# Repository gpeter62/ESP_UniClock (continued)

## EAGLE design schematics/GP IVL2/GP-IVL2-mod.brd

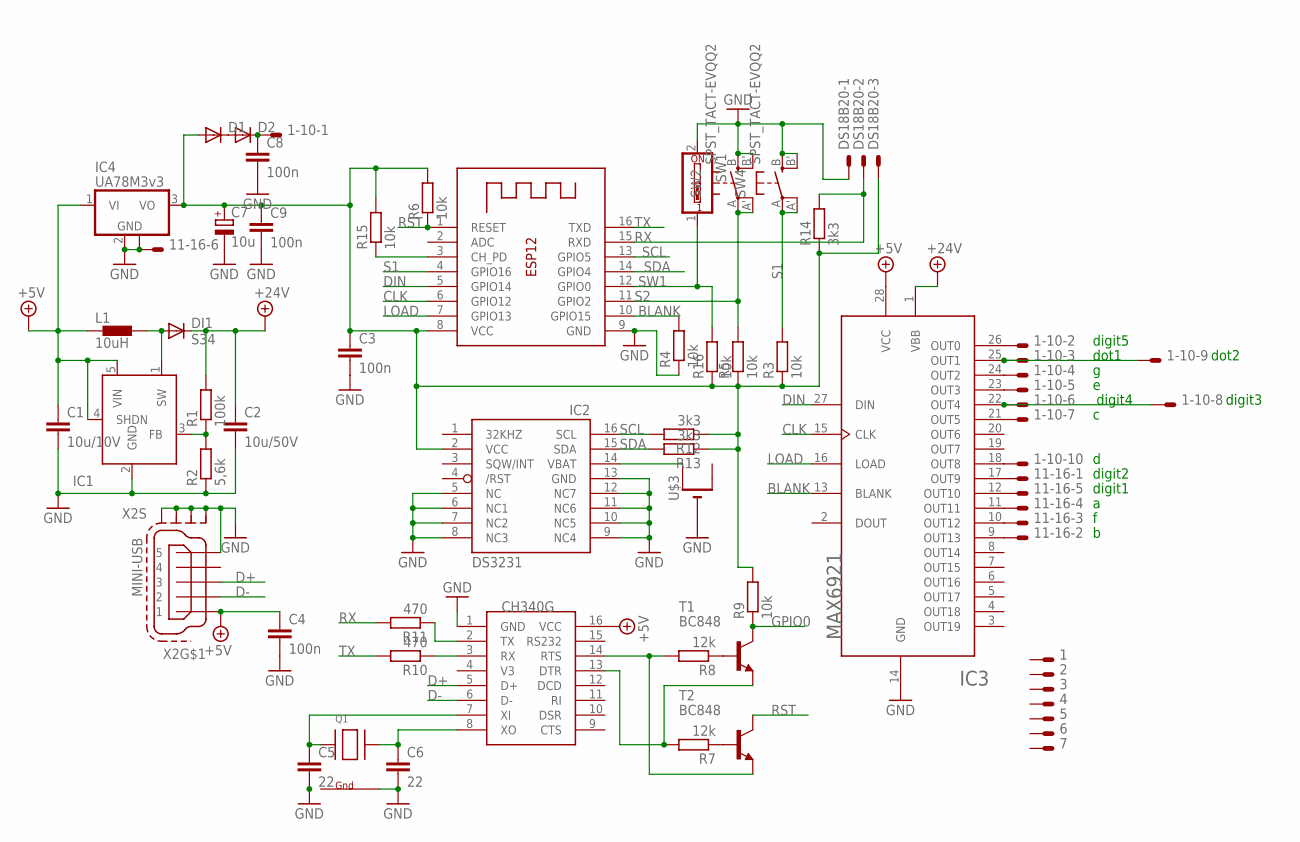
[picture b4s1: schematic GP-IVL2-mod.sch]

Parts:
1: 1; PAD1
1-10: 1-10; PAD10
2: 2; PAD1
3: 3; PAD1
4: 4; PAD1
5: 5; PAD1
6: 6; PAD1
7: 7; PAD1
11-16: 11-16; PAD6
C1: 10u/10V; 1206
C2: 10u/50V; 1206
C3, C4, C8, C9: 100n; C0603
C5, C6: 22; C0603
C7: 10u; E1,8-4
D1, D2: DIODE-D-7.5; D-7.5
DI1: S34; DI-214
DS18B20: PAD3
IC1: LT1930; SOT23-5
IC2: DS3231/SO; SO16W
IC3: MAX6921; SO-28W
IC4: UA78M3v3; SOT223
L1: 10uH; DR73A
Q1: XTAL-4-3225; NX3225
R1: 100k; 0603
R2: 5,6k; 0603
R3, R4, R5, R6, R9, R15, R16: 10k; R0603
R7, R8: 12k; R0603
R10, R11: 470; R0603
R12, R13: 3k3; R0603
R14: 3k3; MINI_MELF-0102W
SW1: SW_DIP-1; EDG-01
SW2, SW4: SPST_TACT-EVQQ2; EVQ-Q2
T1, T2: BC848; SOT23
U$1: CH340G; SOIC16
U$3: CR1220SMT; CR1220-SMD
X1: ESP-12
X2: MINI-USB; 32005-201

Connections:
+5V: C1.1, C4.1, IC1.4 (SHDN), IC1.5 (VIN), IC3.28 (VCC), IC4.1 (VI), L1.1, U$1.16 (VCC), X2.1
BLANK: IC3.13 (BLANK), R4.2, X1.10 (GPIO15)
CLK: IC3.15 (CLK), X1.6 (GPIO12)
D+: U$1.5 (D+), X2.3
D-: U$1.6 (D-), X2.2
DIN: IC3.27 (DIN), X1.5 (GPIO14)
G1: Q1.4 (G1)
GND: 11-16.P$6, C1.2, C2.2, C3.2, C4.2, C5.2, C6.2, C7.-, C8.2, C9.2, DS18B20.P$1, IC1.2 (GND), IC2.5 (NC), IC2.6 (NC1), IC2.7 (NC2), IC2.8 (NC3), IC2.9 (NC4), IC2.10 (NC5), IC2.11 (NC6), IC2.12 (NC7), IC2.13 (GND), IC3.14 (GND), IC4.2 (GND), IC4.4 (GND), Q1.2 (G2), R2.1, R4.1, SW1.2, SW2.B (S), SW2.B' (S1), SW4.B (S), SW4.B' (S1), U$1.1 (GND), U$3.-, X1.9 (GND), X2.5, X2.M1 (S1), X2.M2 (S2), X2.M3 (S3), X2.M4 (S4)
GPIO0: R9.1, T1.3 (C)
LOAD: IC3.16 (LOAD), X1.7 (GPIO13)
unnamed: IC1.3 (FB), R1.1, R2.2
unnamed: DI1.A, IC1.1 (SW), L1.2
unnamed: C5.1, Q1.1 (X1), U$1.7 (XI)
unnamed: R15.1, X1.3 (CH_PD)
unnamed: IC2.14 (VBAT), U$3.+$1 (+)
unnamed: R10.1, U$1.3 (RX)
unnamed: R7.1, T2.1 (B)
unnamed: R8.1, T1.1 (B)
unnamed: R8.2, T2.2 (E), U$1.14 (RTS)
unnamed: R7.2, T1.2 (E), U$1.13 (DTR)
unnamed: R11.1, U$1.2 (TX)
unnamed: C6.1, Q1.3 (X2), U$1.8 (XO)
unnamed: D1.C, D2.A
unnamed: 1-10.P$1, C8.1, D2.C
unnamed: 1-10.P$2, IC3.26 (OUT0)
unnamed: 1-10.P$3, 1-10.P$9, IC3.25 (OUT1)
unnamed: 1-10.P$4, IC3.24 (OUT2)
unnamed: 1-10.P$5, IC3.23 (OUT3)
unnamed: C3.1, C7.+, C9.1, D1.A, DS18B20.P$3, IC2.2 (VCC), IC4.3 (VO), R3.1, R5.1, R6.2, R9.2, R12.1, R13.1, R14.1, R15.2, R16.1, X1.8 (VCC)
unnamed: 1-10.P$6, 1-10.P$8, IC3.22 (OUT4)
unnamed: 1-10.P$7, IC3.21 (OUT5)
unnamed: 1-10.P$10, IC3.18 (OUT8)
unnamed: 11-16.P$1, IC3.17 (OUT9)
unnamed: 11-16.P$5, IC3.12 (OUT10)
unnamed: 11-16.P$4, IC3.11 (OUT11)
unnamed: 11-16.P$3, IC3.10 (OUT12)
unnamed: 11-16.P$2, IC3.9 (OUT13)
RST: R6.1, T2.3 (C), X1.1 (RESET)
RX: DS18B20.P$2, R11.2, R14.2, X1.15 (RXD)
S1: R3.2, SW4.A, SW4.A' (P1), X1.4 (GPIO16)
S2: R5.2, SW2.A, SW2.A' (P1), X1.11 (GPIO2)
SCL: IC2.16 (SCL), R12.2, X1.14 (GPIO4)
SDA: IC2.15 (SDA), R13.2, X1.13 (GPIO5)
SW1: R16.2, SW1.1, X1.12 (GPIO0)
TX: R10.2, X1.16 (TXD)
VBB: C2.1, DI1.K (C), IC3.1 (VBB), R1.2

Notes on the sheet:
digit1
digit2
digit3
digit5
dot1
dot2
digit4

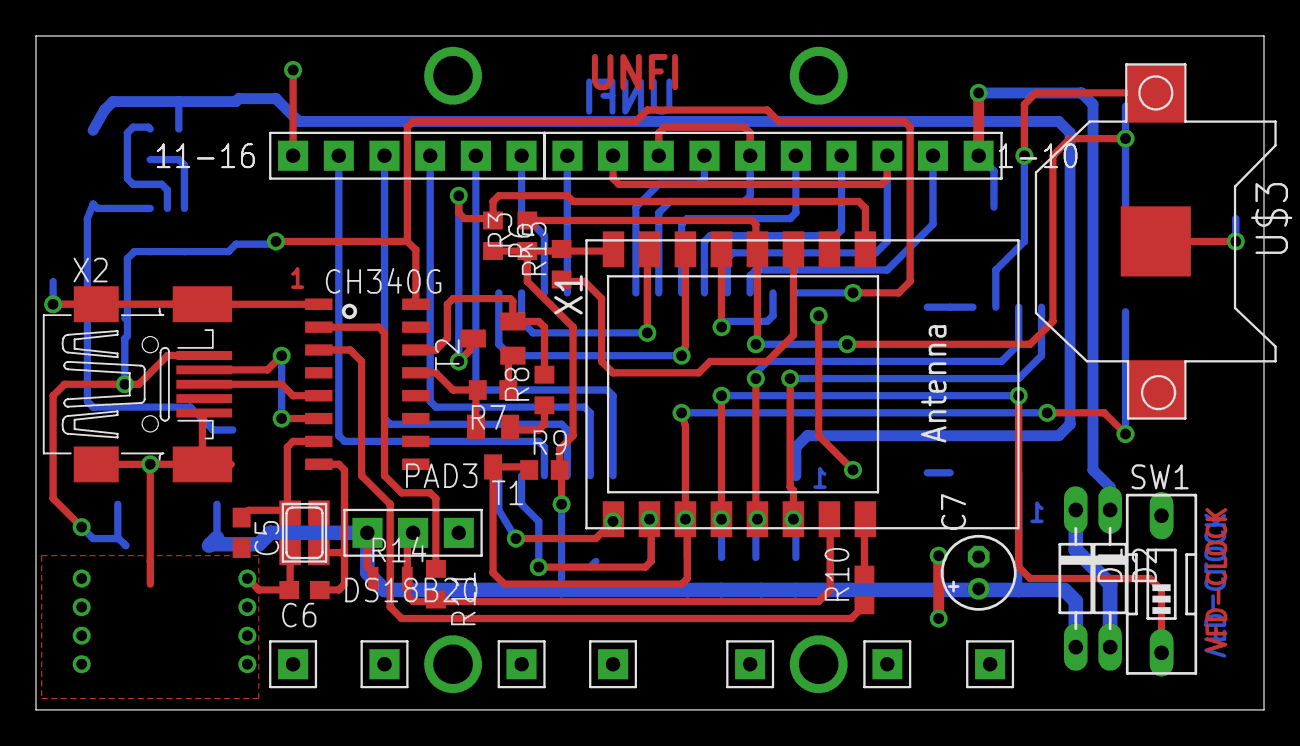
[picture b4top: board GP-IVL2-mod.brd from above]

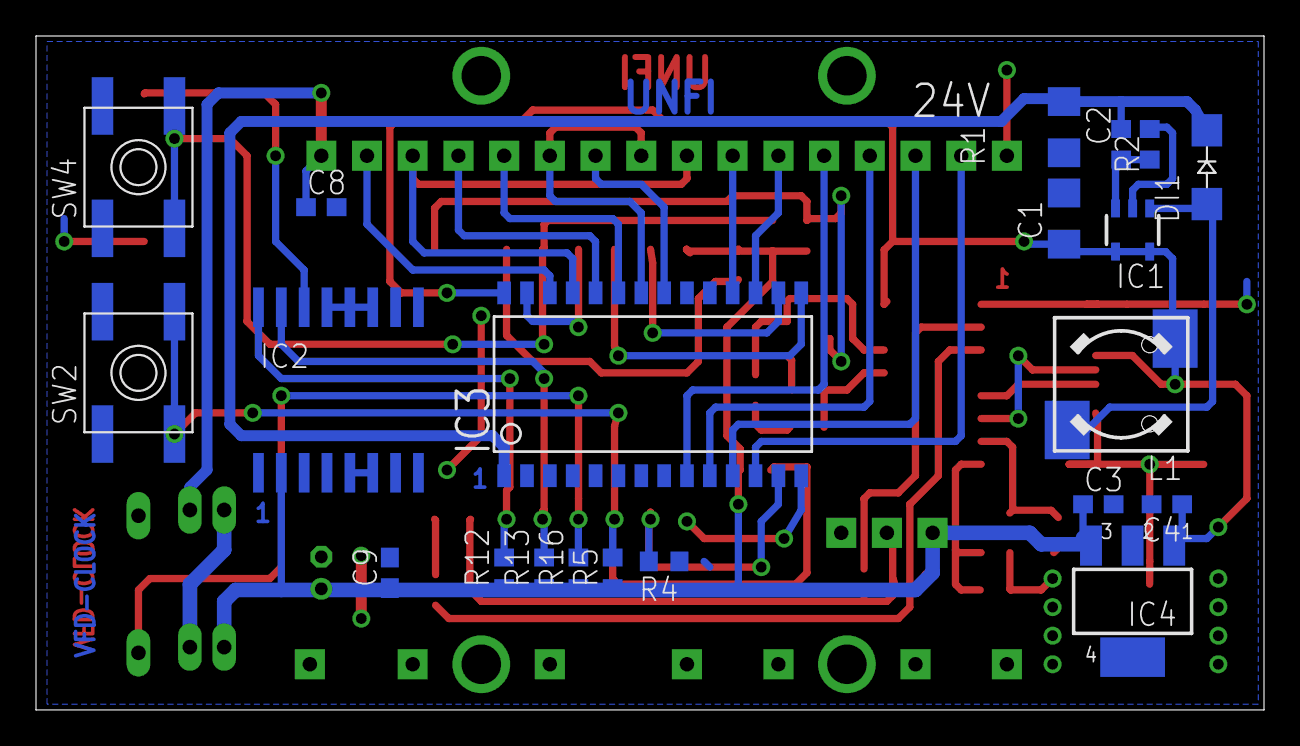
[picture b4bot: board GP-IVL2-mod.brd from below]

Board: 2 copper layers, 68.2 x 37.5 mm, 53 parts (21 on the bottom side), 45 nets.

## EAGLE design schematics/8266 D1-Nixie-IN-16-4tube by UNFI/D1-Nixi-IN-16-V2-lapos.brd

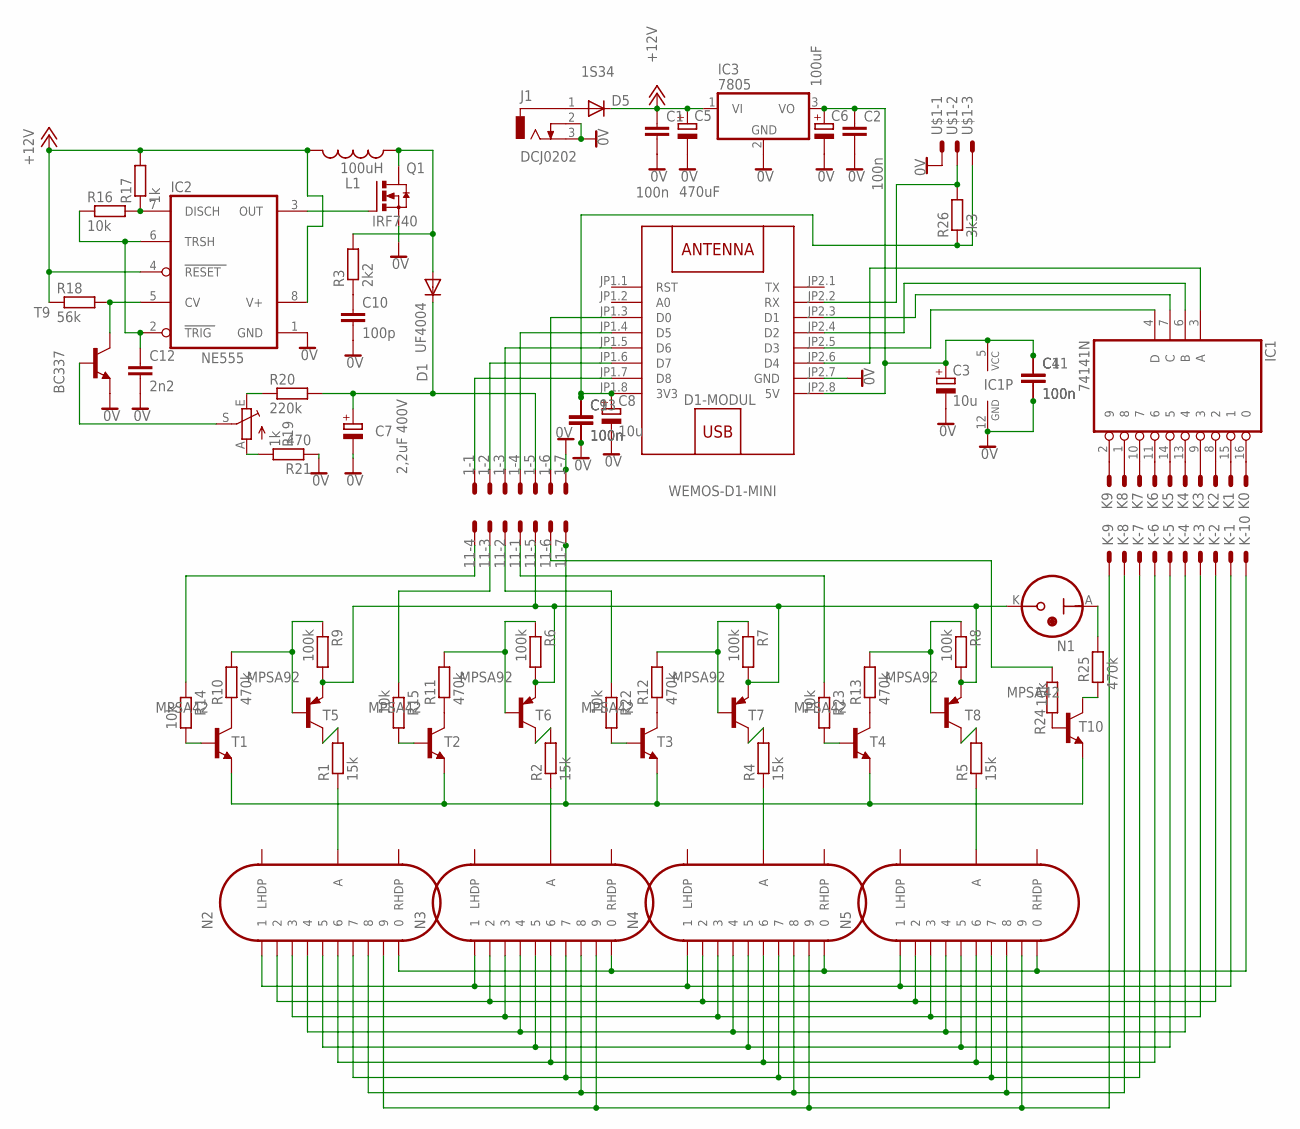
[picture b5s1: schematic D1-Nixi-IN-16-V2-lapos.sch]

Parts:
1, 11: PAD7
C1, C2, C4, C9, C11, C13: 100n; C0603
C3, C8: 10u; E2,5-6E
C5: 470uF; E5-10,5
C6: 100uF; E5-10,5
C7: 2,2uF 400V; E5-10,5
C10: 100p; C050-024X044
C12: 2n2; C0603
D1: UF4004; DO35-10
D1-MODUL: WEMOS-D1-MINI
D5: 1S34; DO214AA
IC1: 74141N; DIL16
IC2: NE555; DIL08
IC3: 7805; TO220H
J1: DCJ0202
K: PAD25
K0, K1, K2, K3, K4, K5, K6, K7, K8, K9: PAD1
L1: 100uH; 6000
N1: IN-6
N2, N3, N4, N5: IN-16
Q1: IRF740; TO220BH
R1, R2, R4, R5: 15k; 0207/7
R3: 2k2; 0204/7
R6, R7, R8, R9: 100k; 0207/7
R10, R11, R12, R13, R25: 470k; 0207/7
R14, R15, R22, R23, R24: 10k; 0207/7
R16: 10k; R0603
R17: 1k; R0603
R18: 56k; R0603
R19: 1k; CA6H
R20: 220k; 0204/7
R21: 470; 0204/7
R26: 3k3; R0603
T1, T2, T3, T4, T10: MPSA42; TO92-EBC
T5, T6, T7, T8: MPSA92; TO92-EBC
T9: BC337; SOT23-BEC
U$1: PAD3

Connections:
0V: 1.P$7, C1.2, C2.2, C3.-, C4.2, C5.-, C6.-, C7.-, C8.-, C9.2, C10.2, C11.2, C12.2, C13.2, D1-MODUL.JP2.7 (GND), IC1.12 (GND), IC2.1 (GND), IC3.2 (GND), J1.2, J1.3, Q1.S, R21.1, T9.E, U$1.P$1
+12V: C1.1, C5.+, D5.C, IC2.4 (RESET), IC2.8 (V+), IC3.1 (VI), L1.1, R17.2, R18.1
GND: 11.P$7, T1.E, T2.E, T3.E, T4.E, T10.E
unnamed: D1-MODUL.JP2.5 (D3), IC1.4 (D)
unnamed: D1-MODUL.JP2.3 (D1), IC1.7 (C)
unnamed: D1-MODUL.JP2.4 (D2), IC1.6 (B)
unnamed: 1.P$1, D1-MODUL.JP1.7 (D8)
unnamed: 1.P$2, D1-MODUL.JP1.6 (D7)
unnamed: 1.P$3, D1-MODUL.JP1.5 (D6)
unnamed: 1.P$4, D1-MODUL.JP1.4 (D5)
unnamed: 1.P$6, D1-MODUL.JP1.3 (D0)
unnamed: N2.A, R1.1
unnamed: N3.A, R2.1
unnamed: N4.A, R4.1
unnamed: N5.A, R5.1
unnamed: R1.2, T5.C
unnamed: R2.2, T6.C
unnamed: R4.2, T7.C
unnamed: R5.2, T8.C
unnamed: R19.E, R20.1
unnamed: R10.1, T1.C
unnamed: R19.A, R21.2
unnamed: R9.1, R10.2, T5.B
unnamed: IC2.3 (OUT), Q1.G
unnamed: IC2.7 (DISCH), R16.2, R17.1
unnamed: C12.1, IC2.2 (TRIG), IC2.6 (TRSH), R16.1
unnamed: R6.1, R11.2, T6.B
unnamed: IC2.5 (CV), R18.2, T9.C
unnamed: C10.1, R3.1
unnamed: 1.P$5, C7.+, D1.C, R20.2
unnamed: R7.1, R12.2, T7.B
unnamed: R8.1, R13.2, T8.B
unnamed: R11.1, T2.C
unnamed: R12.1, T3.C
unnamed: R13.1, T4.C
unnamed: R14.2, T1.B
unnamed: R15.2, T2.B
unnamed: R22.2, T3.B
unnamed: R23.2, T4.B
unnamed: R24.2, T10.B
unnamed: 11.P$5, N1.K, R6.2, R7.2, R8.2, R9.2, T5.E, T6.E, T7.E, T8.E
unnamed: R25.1, T10.C
unnamed: N1.A, R25.2
unnamed: K.P$10, N2.0, N3.0, N4.0, N5.0
unnamed: D1.A, L1.2, Q1.D, R3.2
unnamed: K.P$1, N2.1, N3.1, N4.1, N5.1
unnamed: IC1.15 (1), K1.1
unnamed: IC1.8 (2), K2.1
unnamed: IC1.9 (3), K3.1
unnamed: IC1.13 (4), K4.1
unnamed: IC1.14 (5), K5.1
unnamed: IC1.11 (6), K6.1
unnamed: IC1.10 (7), K7.1
unnamed: IC1.1 (8), K8.1
unnamed: IC1.2 (9), K9.1
unnamed: IC1.16 (0), K0.1
unnamed: K.P$2, N2.2, N3.2, N4.2, N5.2
unnamed: K.P$3, N2.3, N3.3, N4.3, N5.3
unnamed: K.P$4, N2.4, N3.4, N4.4, N5.4
unnamed: K.P$5, N2.5, N3.5, N4.5, N5.5
unnamed: D5.A, J1.1
unnamed: K.P$6, N2.6, N3.6, N4.6, N5.6
unnamed: K.P$7, N2.7, N3.7, N4.7, N5.7
unnamed: K.P$8, N2.8, N3.8, N4.8, N5.8
unnamed: K.P$9, N2.9, N3.9, N4.9, N5.9
unnamed: 11.P$4, R14.1
unnamed: 11.P$3, R15.1
unnamed: 11.P$2, R22.1
unnamed: 11.P$1, R23.1
unnamed: 11.P$6, R24.1
unnamed: C2.1, C3.+, C4.1, C6.+, C11.1, D1-MODUL.JP2.8 (5V), IC1.5 (VCC), IC3.3 (VO)
unnamed: D1-MODUL.JP2.6 (D4), IC1.3 (A)
unnamed: C8.+, C9.1, C13.1, D1-MODUL.JP1.8 (3V3), R26.1, U$1.P$3
unnamed: D1-MODUL.JP2.2 (RX), R26.2, U$1.P$2
unnamed: R19.S, T9.B

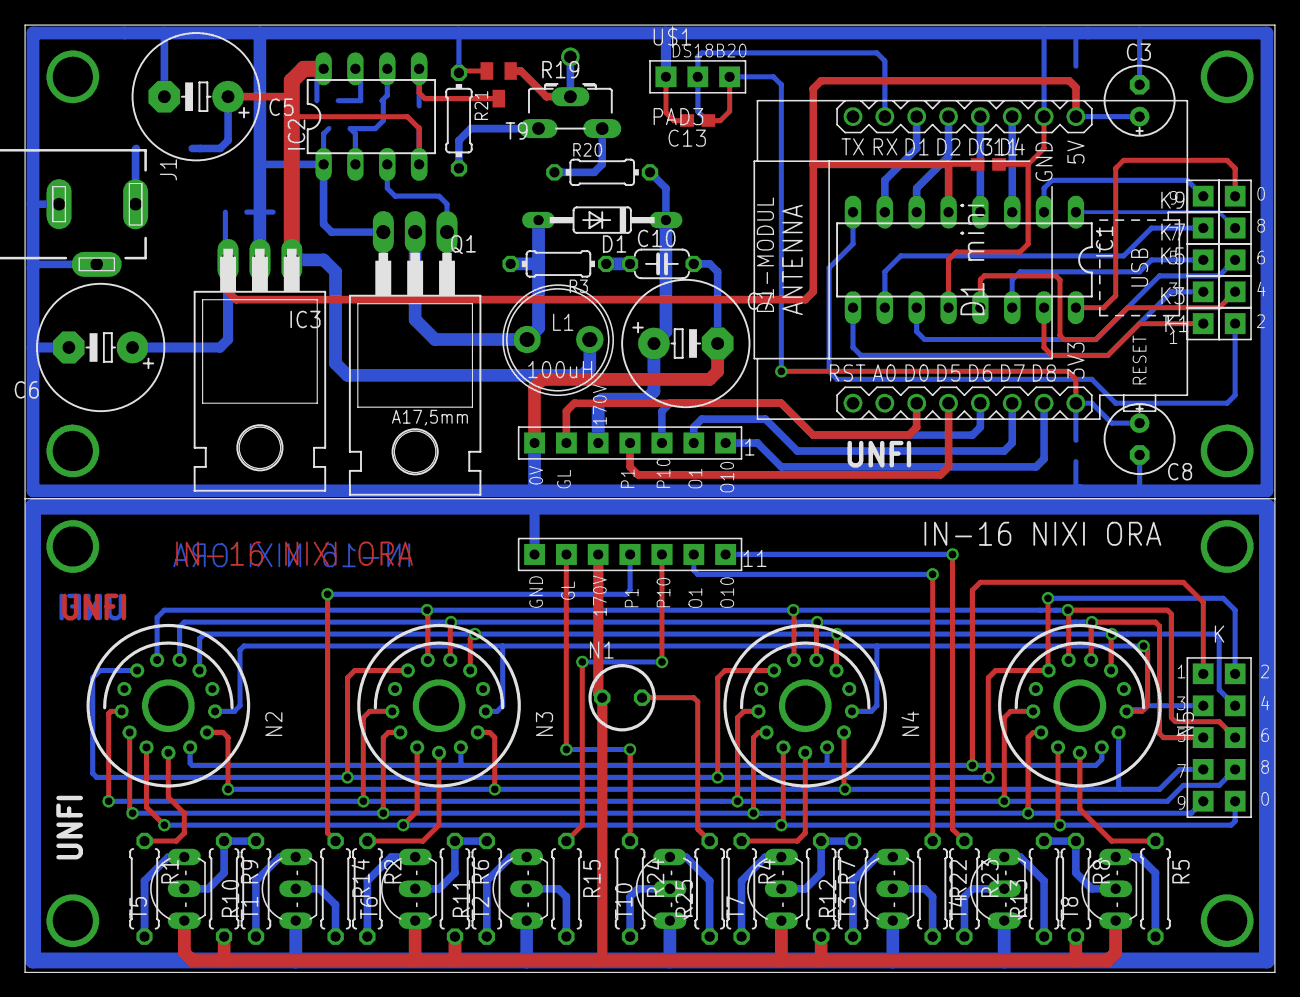
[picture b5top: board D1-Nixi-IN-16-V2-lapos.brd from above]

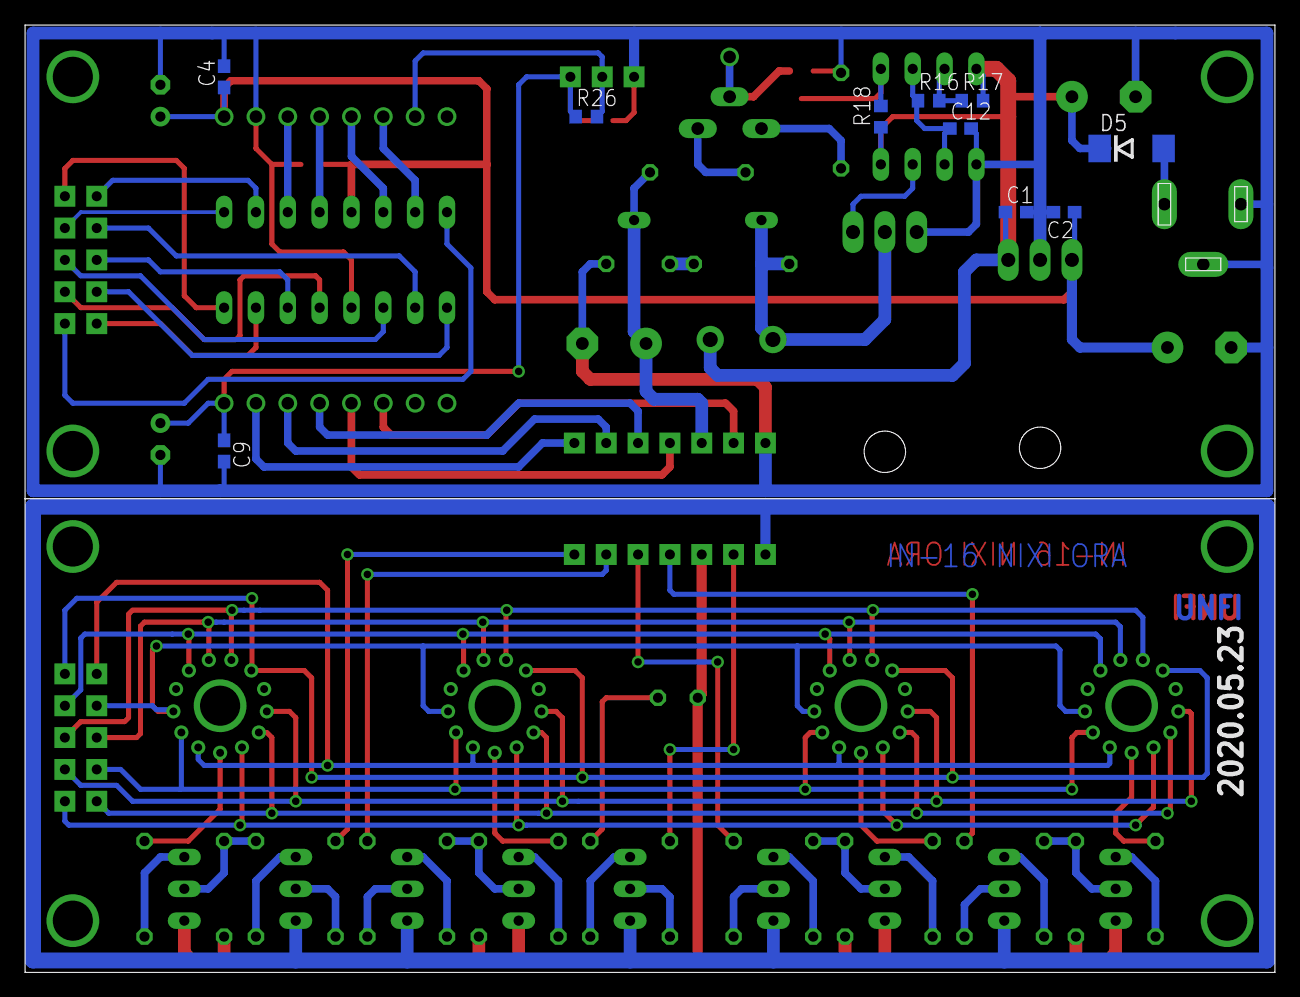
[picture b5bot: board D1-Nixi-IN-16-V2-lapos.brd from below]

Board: 2 copper layers, 99.7 x 75.6 mm, 77 parts (10 on the bottom side), 75 nets.

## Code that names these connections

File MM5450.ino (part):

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// groups share the same 32 segment lines and are multiplexed in time.

//MM5450 control pins (GPIO numbers - see clocks.h D5pin/D6pin/etc for the NodeMCU Dx aliases:
// GPIO14=D5, GPIO12=D6, GPIO13=D7, GPIO15=D8)
#define PIN_LE    14  // D5 Shift Register Latch Enable
#define PIN_CLK   12  // D6 Shift Register Clock
#define PIN_DATA  13  // D7 Shift Register Data
#define PIN_BR    15  // D8 Shift Register Brightness (chip-enable/blank output, active HIGH)

// Bitmasks for the same pins, used with WRITE_PERI_REG(PIN_OUT_SET/CLEAR, ...) for fast
// direct GPIO register access inside the ISR (digitalWrite() is too slow/has too much
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
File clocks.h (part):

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//#define CLOCK_12  //8266 VFD Clock with PT6355 chip
//#define CLOCK_13   //8266 GP PCB v1 clock with 4x IV-16 Numitron tubes + GPS timesync (white box)
//#define CLOCK_14  //8266 6X LD8035 VFD-clock
//#define CLOCK_15  //8266 6X IV-6 VFD-clock RGB
//#define CLOCK_15a  //8266 6X IV-6 VFD-clock RGB
//#define CLOCK_16  //8266 4X IV-6, 1X LD8035
//#define CLOCK_17  //8266 + PT6311 4X IV-22, russian clock
//#define CLOCK_18  //8266 IV-18 VFD-clock RGB
//#define CLOCK_20  //8266 D1-mini, P.S. PCB 4xIN14 clock-thermometer
//#define CLOCK_21  //8266 D1-mini, P.S. PCB 4xIN14 thermometer / humidity
//#define CLOCK_22  //8266 NODEMCU, P.S. PCB 4xIN14 thermometer / humidity
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#define PIN_LE    12  // D6 Shift Register Latch Enable
#define PIN_CLK   13  // D7 Shift Register Clock
#define PIN_DATA  14  // D5 Shift Register Data
#define PIN_BL    15  // D8 Shift Register Blank (1=display off     0=display on)
#define AP_NAME "UNICLOCK"
#define AP_PASSWORD ""
#define WEBNAME "IV-18 VFD Clock"
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#define PIN_LE    12  // D6 Shift Register Latch Enable
#define PIN_CLK   13  // D7 Shift Register Clock
#define PIN_DATA  14  // D5 Shift Register Data
#define PIN_BL    15  // D8 Shift Register Blank (1=display off     0=display on)
#define USE_NEOPIXEL
byte tubePixels[] = {0, 9, 1, 9, 2, 9, 3}; //4 tubes, single leds, 3 leds not used
//#define RADAR_PIN 21
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#define PIN_LE    13  // D6 Shift Register Latch Enable
#define PIN_CLK   12  // D7 Shift Register Clock
#define PIN_DATA  14  // D5 Shift Register Data
#define PIN_BL    15  // D8 Shift Register Blank (1=display off     0=display on)
#define AP_NAME "UNICLOCK"
#define AP_PASSWORD ""
#define WEBNAME "IVL-2 VFD Clock"
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#define PIN_LE    0  // D3 Shift Register Latch Enable
#define PIN_CLK   2  // D4 Shift Register Clock
#define PIN_DATA  5  // D1 Shift Register Data
#define PIN_BL    15  // D8 Shift Register Blank (1=display off     0=display on)
//#define LIGHT_SENSOR_PIN A0  //Only ADC pins are usable!
//#define MAXIMUM_LUX 100    //Lux level for maximum tube brightness
//#define LUX_CALC_SCALAR   12518931 * 1.2
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#define PIN_LE    0  // D3 Shift Register Latch Enable
#define PIN_CLK   2  // D4 Shift Register Clock
#define PIN_DATA  5  // D1 Shift Register Data
#define PIN_BL    15  // D8 Shift Register Blank (1=display off     0=display on)
#define ALARMSPEAKER_PIN 12   //Alarm buzzer pin                                            
#define ALARMBUTTON_PIN  13   //Alarm switch off button pin 
#define ALARM_ON HIGH         //How to switch ON alarm buzzer
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#define PIN_LE    12  // D3 Shift Register Latch Enable
#define PIN_CLK   14  // D4 Shift Register Clock
#define PIN_DATA  15  // D1 Shift Register Data
#define PIN_BL    4  // D8 Shift Register Blank (1=display off     0=display on)
//#define LIGHT_SENSOR_PIN A0  //Only ADC pins are usable!
//#define MAXIMUM_LUX 100    //Lux level for maximum tube brightness
//#define LUX_CALC_SCALAR   12518931 * 1.2
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#define PIN_LE    0  // D3 Shift Register Latch Enable
#define PIN_CLK   2  // D4 Shift Register Clock
#define PIN_DATA  5  // D1 Shift Register Data
#define PIN_BL    15  // D8 Shift Register Blank (1=display off     0=display on)
//#define LIGHT_SENSOR_PIN A0  //Only ADC pins are usable!
//#define MAXIMUM_LUX 100    //Lux level for maximum tube brightness
//#define LUX_CALC_SCALAR   12518931 * 1.2
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byte digitEnablePins[] = {0, 1, 2, 3};
//PT6311 pins
#define PIN_CLK  14   //  Clock
#define PIN_DIN  13   //  DataIN
#define PIN_LOAD 15   //  STB pin 
//#define LIGHT_SENSOR_PIN A0  //Only ADC pins are usable!
//#define MAXIMUM_LUX 100    //Lux level for maximum tube brightness
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#define PIN_LE    4  // D4 Shift Register Latch Enable
#define PIN_CLK   5  // D1 Shift Register Clock
#define PIN_DATA  2  // D4 Shift Register Data
#define PIN_BL    14  // D5 Shift Register Blank (1=display off     0=display on)
#define ALARMSPEAKER_PIN 16   //Alarm buzzer pin                                            
#define ALARMBUTTON_PIN  13   //Alarm switch off button pin 
#define ALARM_ON HIGH         //How to switch ON alarm buzzer
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#define PIN_LE    4  // Shift Register Latch Enable
#define PIN_CLK   17  // Shift Register Clock
#define PIN_DATA  16  // Shift Register Data
#define PIN_BL    32  // Shift Register Blank (1=display off     0=display on)
#define ALARMSPEAKER_PIN 2   //Alarm buzzer pin                                            
#define ALARMBUTTON_PIN 0    //Alarm switch off button pin 
#define ALARM_ON HIGH         //How to switch ON alarm buzzer
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#define PIN_LE    14  // Shift Register Latch Enable
#define PIN_CLK   13  // Shift Register Clock
#define PIN_DATA  27  // Shift Register Data
#define PIN_BL    12  // Shift Register Blank (1=display off     0=display on)
//#define PIN_SDA 21          // you can set the used SDA and SCL pins
//#define PIN_SCL 22           // if it is not default value
#define ALARMSPEAKER_PIN 33   //Alarm buzzer pin                                            
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#define PIN_LE    14  // Shift Register Latch Enable
#define PIN_CLK   13  // Shift Register Clock
#define PIN_DATA  27  // Shift Register Data
#define PIN_BL    12  // Shift Register Blank (1=display off     0=display on)
//#define ALARMSPEAKER_PIN 33   //Alarm buzzer pin
#define ALARMBUTTON_PIN 32    //Alarm switch off button pin 
#define ALARM_ON HIGH         //How to switch ON alarm buzzer
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#define PIN_LE    4  // Shift Register Latch Enable
#define PIN_CLK   17  // Shift Register Clock
#define PIN_DATA  16  // Shift Register Data
#define PIN_BL    32  // Shift Register Blank (1=display off     0=display on)
#define ALARMSPEAKER_PIN 2   //Alarm buzzer pin                                            
#define ALARMBUTTON_PIN 0    //Alarm switch off button pin
#define TUBE_POWER_PIN 23
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#define PIN_LE    22  // Shift Register Latch Enable
#define PIN_CLK   17  // Shift Register Clock
#define PIN_DATA  16  // Shift Register Data
#define PIN_BL    21  // Shift Register Blank (1=display off     0=display on)
#define ALARMSPEAKER_PIN 2   //Alarm buzzer pin                                            
#define ALARMBUTTON_PIN 0    //Alarm switch off button pin
#define TUBE_POWER_PIN 23
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#define PIN_LE    4  // Shift Register Latch Enable
#define PIN_CLK   17  // Shift Register Clock
#define PIN_DATA  16  // Shift Register Data
#define PIN_BL    32  // Shift Register Blank (1=display off     0=display on)
#define ALARMSPEAKER_PIN 2   //Alarm buzzer pin                                            
#define ALARMBUTTON_PIN 0    //Alarm switch off button pin
#define TUBE_POWER_PIN 27
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#define PIN_LE    4  // Shift Register Latch Enable
#define PIN_CLK   17  // Shift Register Clock
#define PIN_DATA  16  // Shift Register Data
#define PIN_BL    32  // Shift Register Blank (1=display off     0=display on)
#define ALARMSPEAKER_PIN 2   //Alarm buzzer pin                                            
#define ALARMBUTTON_PIN 0    //Alarm switch off button pin
#define TUBE_POWER_PIN 27
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#define USE_BH1750            //I2C luxmeter sensor
//_______________________________ HV5122 setup ____________________________________________________
#define NEWHV5122
#define PIN_DIN  22   // DataIn  - chip0 DOUT pin is connected to chip1 DIN pin!
#define PIN_CLK  17   // Clock
#define PIN_OE   21   // OutputEnable
#define MAXDIGITS 6
int maxDigits = MAXDIGITS;
byte digitPins[MAXDIGITS + 1][10] = {          ////Data pin numbers 100+ means: chip1 pins are used. Chip0's DOUT is connected to chip1's DIN
  {2, 10, 9, 8, 7, 6, 5, 4, 3, 1},             //sec  1 , chip0  (tube#0)
  {11, 32, 20, 19, 18, 17, 16, 15, 14, 13},    //sec  10 , chip0 (tube#1)
  {22, 31, 29, 30, 27, 28, 25, 26, 23, 24},    //min   1 , chip0 (tube#2)
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//#define MASTER_RADAR_TOPIC       "homeassistant/sensor/10521c5e14c4/radar/state"
//_______________________________ HV5122 setup ____________________________________________________
#define NEWHV5122
#define PIN_DIN  22   // DataIn  - chip0 DOUT pin is connected to chip1 DIN pin!
#define PIN_CLK  17   // Clock
#define PIN_OE   21   // OutputEnable
#define MAXDIGITS 6
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#define PIN_SCL 26               //D2
//_______________________________ HV5122 setup ____________________________________________________
#define NEWHV5122
#define PIN_DIN  16   // DataIn  - chip0 DOUT pin is connected to chip1 DIN pin!
#define PIN_CLK  17   // Clock
#define PIN_OE   21   // OutputEnable
#define MAXDIGITS 6
int maxDigits = MAXDIGITS;
byte digitPins[MAXDIGITS + 1][10] = {          ////Data pin numbers 100+ means: chip1 pins are used. Chip0's DOUT is connected to chip1's DIN
  {126, 127, 128, 130, 124, 123, 132, 131, 129, 125},   //hour 10 , CHIP0
  {116, 117, 118, 120, 114, 113, 122, 121, 119, 115},   //hour 1 , CHIP0
  {104, 105, 106, 108, 102, 101, 110, 109, 107, 103},   //min 10 , CHIP0
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
//_______________________________ HV5122 setup ____________________________________________________
#define NEWHV5122
#define PIN_DIN  5   // DataIn  - chip0 DOUT pin is connected to chip1 DIN pin!
#define PIN_CLK  0   // Clock
#define PIN_OE   4   // OutputEnable
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
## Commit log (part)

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2020-05-06 Add files via upload
    Animation may happen when the numbers are changing.
    Animation mode setting is on clock's web page.
    0 = disable
    1 = serial animation
    2 = paralel animation
2020-05-07 Add files via upload
    4 different animation mode
    Animation mode=5 means random animation
2020-05-17 Add files via upload
    New animation mode
2020-05-18 Add files via upload
    Individual brightness level setup possibility for each tube (digit)...
2020-05-18 Add files via upload
    Numitron Clock schematic and board
2020-05-28 Add files via upload
    GPS sync modul
2020-06-16 Add files via upload
    GPS sync and double thermometer upgrade...
2020-07-18 Add files via upload
    DHxx sensors added
2020-08-18 Add files via upload
    PCF8574 digit driver version working.
2020-10-06 upgrade
2020-10-21 Add files via upload
    Some tuning
2020-10-22 Add files via upload
    Rainbow effect
2020-10-23 Add files via upload
    update
2020-10-23 initial Web ui release
2020-10-23 small fix
2020-10-24 test communication draft
2020-10-24 JSON parameters first version
2020-10-24 Add files via upload
    Final version with old web page design.
2020-10-24 small changes regarding config parameters
2020-10-24 Json ready
2020-10-24 communication updated
2020-10-24 config save test
2020-10-24 use server's config
2020-10-24 use server time
2020-10-25 fixed send message
2020-10-25 changed get and post
2020-10-25 mobile css fixed
2020-10-25 Ardu code update
2020-10-25 fixing switch bug
2020-10-25 kis fix
2020-10-27 Uniclock v2
2020-10-27 some bugfix
2020-10-27 bugfix
2020-10-28 fixing html
2020-10-28 Lot of bugfix!
2020-10-28 UniCLock v2.0 version
2020-10-28 testTubes() switched back...:)
2020-10-29 RGB led tuning
2020-10-29 RGB update
2020-10-29 RGB led effect tuning
2020-11-01 Neopixel upgrade
2020-11-03 NeoPixel upgrade: Knight Rider's KITT effect...:)
2020-11-03 neoPixel...
2020-11-16 schematic update
2020-11-17 ESP32 version
2020-11-17 Add files via upload
    V2.0 backup
2020-11-18 esp32 upgrade
2020-11-20 Add files via upload
    Neopixel tuning
2020-11-22 version to header, favicon, hide non relevant box
2020-11-22 ESP32 bugfix
2020-11-22 fix color can be set anytime
2020-11-22 Adatcsere
2020-11-22 get current infos, keiemelések
2020-11-22 Web refresh update
2020-12-01 Neopixel update
2020-12-01 Nopixel upgrade
2020-12-03 ESP32 and Neopixel update
2020-12-04 WebServer speeding up: gzip content supported
2020-12-05 Webserver tuning
2020-12-10 setinterval -> settimeout
2020-12-14 README.md update
2020-12-14 Version Upgrade
2020-12-14 HUN Document update
2020-12-14 extra % character
2020-12-14 Schematics upgrade
2020-12-16 HUN manual update
2020-12-18 Update README.md
    Don't forget! ...
2020-12-18 Update README.md
    don't forget...
2020-12-20 schematics update
2020-12-22 Schematics with PCB upload
2020-12-25 some update, Z573/Z574 decimal point usage
2020-12-27 clocks.h tuning
2020-12-29 Manuals update!
2021-01-06 No restart, if wifi lost
2021-01-08 New ESP32 clocks with wemos d1 mini in clocks.h
2021-01-09 PCF_multiplex update
2021-01-11 DHT sensor update
2021-01-12 PCF update
2021-01-12 Dallas temp update
2021-01-12 PCF multiplex update
2021-01-12 5sec ->20sec web page refresh
2021-01-13 Sensor refresh update
2021-01-14 HV5122 Nixie driver alpha version
2021-01-14 HV5122
2021-01-17 Some tuning on temperature display
2021-01-21 ESP_UniClock v2.5 upgrade!
2021-01-21 all_lib.zip: All libraries update
2021-01-23 2.5 update (alpha version, under testing)
2021-01-23 HUN doc update
2021-01-23 PDF Manual v2_5
2021-01-24 SHT21 sensor tested!
2021-01-25 2.5 final version
2021-01-25 v2.5 final - 2 temperature and humidity on webpage
2021-01-25 Radar & LIGHTSENS improvement
2021-01-26 some tuning
2021-01-26 not needed
2021-01-26 DATE_REPEAT_MIN parameter
2021-01-28 Liuxmeter tuning
2021-02-03 Home-assistant integration with MQTT
2021-02-09 MQTT
2021-02-13 ESP32 - HV5122 6x tubes clock working!
2021-02-13 HV5122 clock
2021-02-15 8266 DNSserver bugfix
2021-02-16 HV5122 blinking dots update
2021-02-20 Variable luxValue changed to lx (Compiler error)
2021-03-02 ESP32 Numitron clock beta version
2021-03-08 ESP32 Numitron + BH1750 lux sensor tested
2021-03-12 LDR measure/brightness control update
2021-03-12 RTC function update
2021-03-18 New fields added
2021-03-18 Add files via upload
    New parameter fields
    New timesync (timeserver/RTC/GPS)
    MQTT update
2021-03-19 Add files via upload
    Nyers bővitett index.html
2021-03-19 Add files via upload
    Some change
2021-03-19 PCB available
2021-03-19 New photos (ESP32_Numitron)
2021-03-19 pagination added
2021-03-19 Add files via upload
    Bővítve, javítva
2021-03-21 small changes
2021-03-22 sliders, info-popups, text inputs, color, small fixes
2021-03-22 date mode
2021-03-23 celsius fahrenheit
2021-03-24 Add files via upload
    Backup program source
2021-03-24 program backup
2021-03-24 UniClock v3.0 beta
2021-03-24 v3.0 bugfix
2021-03-24 V3.0
2021-03-25 MAXBRIGHTNESS change from 10 to 100
2021-03-25 V3 bugfix
2021-03-26 fw update
2021-03-27 settings page
2021-03-27 Clock details info on web page
2021-03-30 Web update
2021-03-30 timezone / DST settings
2021-03-31 clocks.h update
2021-03-31 Numitron clock ini fix
2021-04-01 GPS update
2021-04-04 wifi/AP mode switch on web page
2021-04-05 TOM025 clock setup. :)
2021-04-05 small bug
2021-04-05 Sensor correction on web page
2021-04-06 web page humidity display bugfix
2021-04-06 RADAR_TIMEOUT change from sec to min
2021-04-06 Cathode Protect procedure
2021-04-06 lenyomva ne tűnjön el a slider info és azonnal frissítse a C/F kiírást
2021-04-06 some update
2021-04-06 show info immedietly after click
2021-04-07 Radar timeout check bugfix
2021-04-07 CLOCK_42 pin update
2021-04-12 Radar timeout update
    HV5122 slower timing
2021-04-14 web page works without switching off tubes...
2021-04-15 libraries update
2021-04-15 EspExceptionDecoder
2021-04-16 Better wifi connecting
2021-04-19 new CathodeProtect
    HV5122 decpoint
2021-04-21 Small change
2021-04-28 RSSI, OTA
2021-05-11 LDR fix, optional DEFAULT wifisettings, WifiManager
2021-06-05 bugfix + MQTT update
2021-06-08 MULE_V2 PIC change to ESP32
2021-06-08 MULE_V2 fix
2021-06-18 SN75518+IV-17 driver
2021-06-21 SN75518 bugfix
2021-06-28 SN75518 update
2021-08-01 Date format bugfix for 8digit clocks
2021-08-09 Numitron and no_multiplex_ESP32 update
2021-10-31 fix for 8266 3.xx board definitions
2022-01-04 Small fixes and PT6311 VFD driver
2022-01-04 Libraries refreshed to latest version
2022-01-09 Nixie tubes Nnimation#5: some tuning
2022-02-06 NON_MULTIPLEX_ESP32 radar sensor fix
2022-02-06 NON_MULTIPLEX_ESP32 some timing tuning
2022-04-03 VQC10 clock and 1tube clock
2022-04-04 + new wifi handling, VQC10 driver, jquery360
2022-04-04 option: wifimanager is usable
2022-04-04 espsoftwareserial library for gps timesync
2022-04-05 Library update
2022-04-07 New HV5122 driver
2022-04-08 MQTT update, parameters moved to clocks.h
2022-04-11 1tube clock update
2022-04-12 Night: switch off all animations
2022-04-14 MQTT Radar usage bugfix
2022-04-15 Ntpclient library changed
2022-05-06 8266 firmware update bugfix
2022-05-06 K.D. CLOCK_6A clock.h tube fix
2022-06-20 some updates
2022-06-24 RTC handling update, new library
2022-07-03 Library update & small code updates
2022-08-12 new P.S. clock def
2022-09-13 web page & other small updates
2022-09-25 New setting: temperature repeat time (min)
2022-09-25 :) repaired...
2022-09-26 ESP32 2.0.5 boarddef tested!
2022-10-26 Thermometer Clock
2023-03-29 Some fix and new display options:
    #define TEMP_START_POSITION 3 //to define the temperature display digit starting positions
    #define HUMID_START_POSITION 3
    #define DISPLAYTEMP_ONLY_2DIGITS //show now decimals, only 2 digit numbers
    #define DISPLAYHUMID_ONLY_2DIGITS
2023-10-01 Add files via upload
    bugfix
2026-02-05 Update README with Arduino IDE version details
    Clarified compatibility information for Arduino IDE versions.
2026-02-05 Add files via upload
    WordClock Hungarian, German and English language versions
    ESP32
2026-02-05 Add WordClock feature with multilingual support
